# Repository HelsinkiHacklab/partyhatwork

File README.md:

partyhatwork
============

Mesh network of [party][party1]-[hats][hat1], see http://kirjoitusalusta.fi/hacklab-partyhatwork

[party1]: http://www.youtube.com/watch?v=EIru0xmfsWs
[hat1]: http://www.flickr.com/photos/netlcom/7639700776/in/pool-hlt

## Hardware

  * [rev1](./hardware/board_rev1/)

## Software

  * Reference XMegaduino [sketch](./software/arduino/partyhatwork/)
  * [Instructions](https://github.com/HelsinkiHacklab/XMega-boards/tree/master/software/arduino-xmega) for patching XMegaduino to support our board variant
  * [XBee API wrapper](./software/pc/beehive)
  * [Animation builder](http://helsinkihacklab.github.io/partyhatwork/software/pc/animationbuilder/animationbuilder.html)

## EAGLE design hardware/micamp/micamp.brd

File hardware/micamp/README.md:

# Microphone board

Basically this [sparkfun board][sparkmic] but with better mic and suitably adjusted filter values.

[sparkmic]: https://www.sparkfun.com/products/9964

## BOM

  - http://www.digikey.fi/product-detail/en/CMA-4544PF-W/102-1721-ND/1869981
  - http://www.digikey.fi/product-detail/en/OPA344NA%2F250/OPA344NACT-ND/362263
  - Some standard 0603 size caps & resistors which I will enumerate later

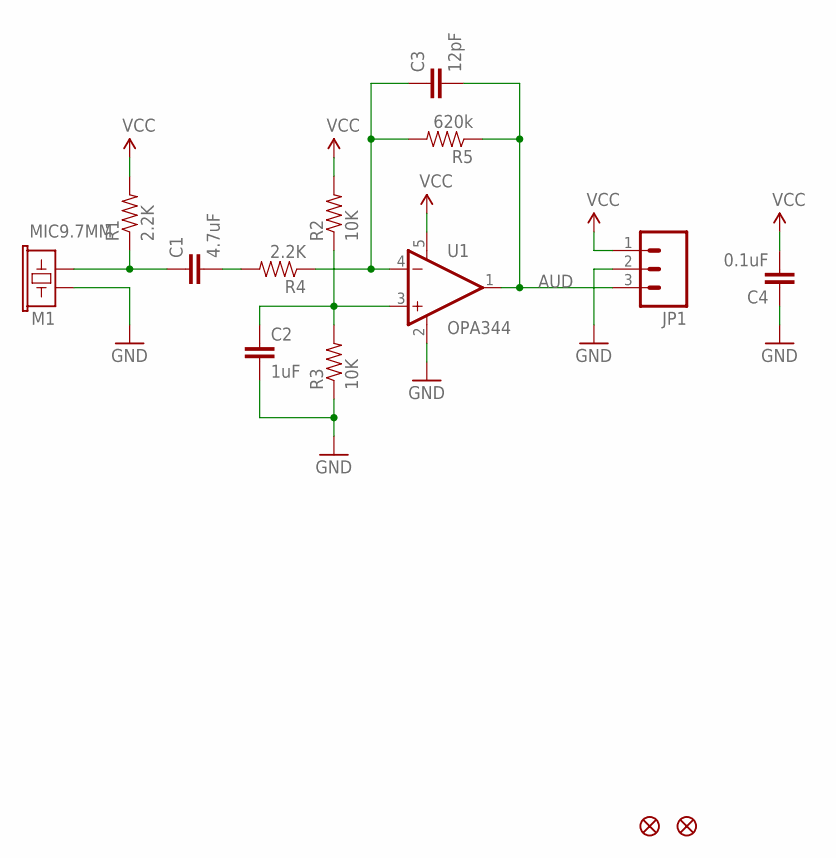
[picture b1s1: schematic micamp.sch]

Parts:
C1: 4.7uF; 0603-CAP
C2: 1uF; 0603-CAP
C3: 12pF; 0603-CAP
C4: 0.1uF; 0603-CAP
JP1: M03PTH; 1X03
JP2, JP3: FIDUCIAL1X2; FIDUCIAL-1X2
M1: MIC9.7MM; MIC-9.7MM
R1, R4: 2.2K; 0603-RES
R2, R3: 10K; 0603-RES
R5: 620k; 0603-RES
U1: OPA344; SOT23-5

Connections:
AUD: C3.2, JP1.3, R5.1, U1.1 (OUT)
GND: C2.2, C4.1, JP1.2, M1.2, R3.1, U1.2 (V-)
unnamed: C1.1, M1.1, R1.1
unnamed: C3.1, R4.1, R5.2, U1.4 (-IN)
unnamed: C1.2, R4.2
unnamed: C2.1, R2.1, R3.2, U1.3 (+IN)
VCC: C4.2, JP1.1, R1.2, R2.2, U1.5 (V+)

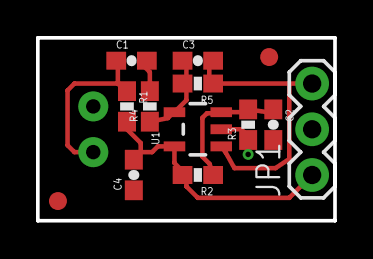
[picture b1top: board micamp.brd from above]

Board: 2 copper layers, 16.5 x 10.2 mm, 14 parts (1 on the bottom side), 7 nets.

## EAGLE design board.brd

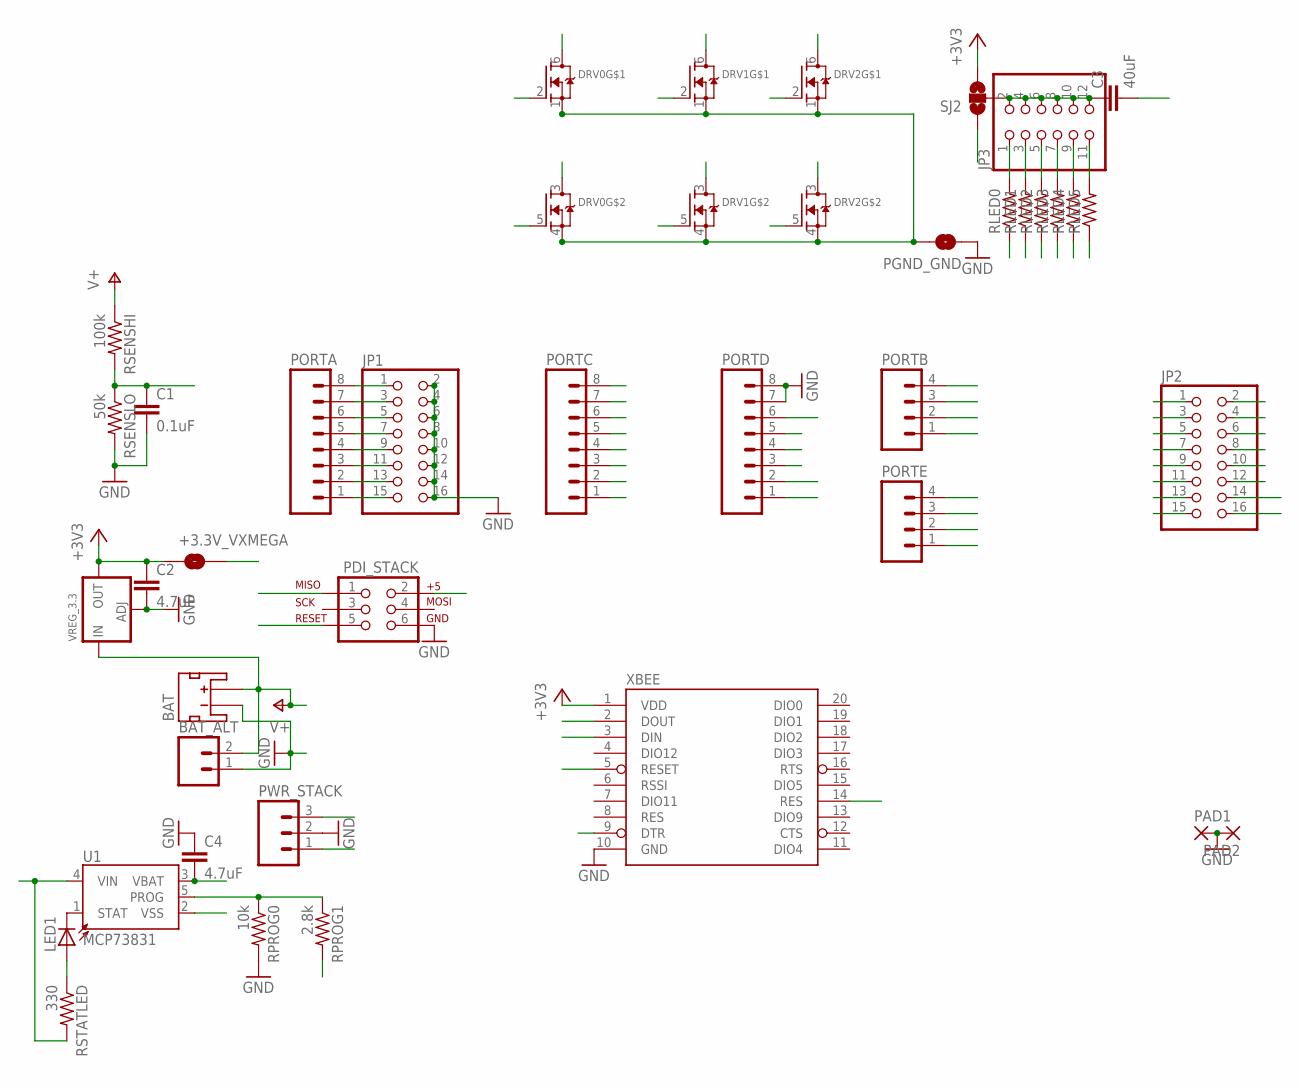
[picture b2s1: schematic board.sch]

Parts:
+3.3V_VXMEGA: SOLDERJUMPERTRACE; SJ_2S-TRACE
BAT: JST_2MM_MALE; JST-2-SMD
BAT_ALT: M02PTH; 1X02
C1: 0.1uF; C0603K
C2: 4.7uF; C0805K
C3: 40uF; C1210
C4: 4.7uF; C0805
DRV0, DRV1, DRV2: MOSFET-N_DUAL; SOT363
JP1: PINHD-2X8; 2X08
JP2: PINHD-2X8/90; 2X08/90
JP3: PINHD-2X6/90; 2X06/90
LED1: LEDCHIP-LED0603; CHIP-LED0603
PAD1, PAD2: 3,81/1,4
PDI_STACK: AVR_SPI_PRG_6NS; 2X3-NS
PGND_GND: SOLDERJUMPERTRACE; SJ_2S-TRACE
PORTA: M081X08; 1X08
PORTB: M04PTH; 1X04
PORTC: M081X08; 1X08
PORTD: M081X08; 1X08
PORTE: M04PTH; 1X04
PWR_STACK: M03PTH; 1X03
RLED0, RLED1, RLED2, RLED3, RLED4, RLED5: R-US_R0805; R0805
RPROG0: 10k; R0603
RPROG1: 2.8k; R0603
RSENSHI: 100k; R0603
RSENSLO: 50k; R0603
RSTATLED: 330; R0603
SJ2: SOLDERJUMPER_2WAY-OLDT; SJ_2
U1: MCP73831; SOT23-5
VREG_3.3: LM1117SOT223-WAVE; SOT223-W
XBEE: XBEE-1B2; XBEE-SILK

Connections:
+3V3: +3.3V_VXMEGA.1, C2.1, JP2.2, SJ2.3, VREG_3.3.2 (OUT), XBEE.1 (VDD)
GND: BAT.1 (-), BAT_ALT.1, C1.2, C2.2, C4.1, JP1.2, JP1.4, JP1.6, JP1.8, JP1.10, JP1.12, JP1.14, JP1.16, JP2.4, JP2.13, PAD1.1, PAD2.1, PDI_STACK.6, PGND_GND.1, PORTD.7, PORTD.8, PWR_STACK.2, RPROG0.2, RSENSLO.2, U1.2 (VSS), VREG_3.3.1 (ADJ), XBEE.10 (GND), XBEE.14 (RES)
LED0: DRV0.6 (D), RLED0.1
LED0R: JP3.1, RLED0.2
LED1: DRV0.3 (D), RLED1.1
LED1R: JP3.3, RLED1.2
LED2: DRV1.6 (D), RLED2.1
LED2R: JP3.5, RLED2.2
LED3: DRV1.3 (D), RLED3.1
LED3R: JP3.7, RLED3.2
LED4: DRV2.6 (D), RLED4.1
LED4R: JP3.9, RLED4.2
LED5: DRV2.3 (D), RLED5.1
LED5R: JP3.11, RLED5.2
unnamed: LED1.C, U1.1 (STAT)
unnamed: LED1.A, RSTATLED.1
PA0: JP1.15, PORTA.1
PA1: JP1.13, PORTA.2
PA2: JP1.11, PORTA.3
PA3: JP1.9, PORTA.4
PA4: JP1.7, PORTA.5
PA5: JP1.5, PORTA.6
PA6: JP1.3, PORTA.7
PA7: JP1.1, PORTA.8
PB0/XMEGA_AREF: JP2.1, PORTB.1, RPROG1.2
PB1/VBAT_SENSE: C1.1, JP2.3, PORTB.2, RSENSHI.2, RSENSLO.1
PB2: JP2.5, PORTB.3
PB3: JP2.7, PORTB.4
PD0: JP2.9, PORTD.1
PD1: JP2.11, PORTD.2
PD5: JP2.15, PORTD.6
PDI_DATA: PDI_STACK.1
PDI_RESET/CLK: PDI_STACK.5, XBEE.9 (DTR)
PE0/SDA: JP2.6, PORTE.1
PE1/SCL: JP2.8, PORTE.2
PE2: JP2.10, PORTE.3
PE3: JP2.12, PORTE.4
PGND: C3.2, DRV0.1 (S), DRV0.4 (S), DRV1.1 (S), DRV1.4 (S), DRV2.1 (S), DRV2.4 (S), PGND_GND.2
PWM0: DRV0.2 (G), PORTC.1
PWM1: DRV0.5 (G), PORTC.2
PWM2: DRV1.2 (G), PORTC.3
PWM3: DRV1.5 (G), PORTC.4
PWM4: DRV2.2 (G), PORTC.5
PWM5: DRV2.5 (G), PORTC.6
RPROG: RPROG0.1, RPROG1.1, U1.5 (PROG)
VBAT: BAT.2 (+), BAT_ALT.2, C4.2, RSENSHI.1, SJ2.1, U1.3 (VBAT), VREG_3.3.3 (IN)
VLED: C3.1, JP3.2, JP3.4, JP3.6, JP3.8, JP3.10, JP3.12, SJ2.2
VXMEGA: +3.3V_VXMEGA.2, PDI_STACK.2, PWR_STACK.3
VXMEGA_USB: PWR_STACK.1, RSTATLED.2, U1.4 (VIN)
XBEE_RESET: PORTD.5, XBEE.5 (RESET)
XMEGA_RX0: PORTD.3, XBEE.2 (DOUT)
XMEGA_RX1: JP2.14, PORTC.7
XMEGA_TX0: PORTD.4, XBEE.3 (DIN)
XMEGA_TX1: JP2.16, PORTC.8

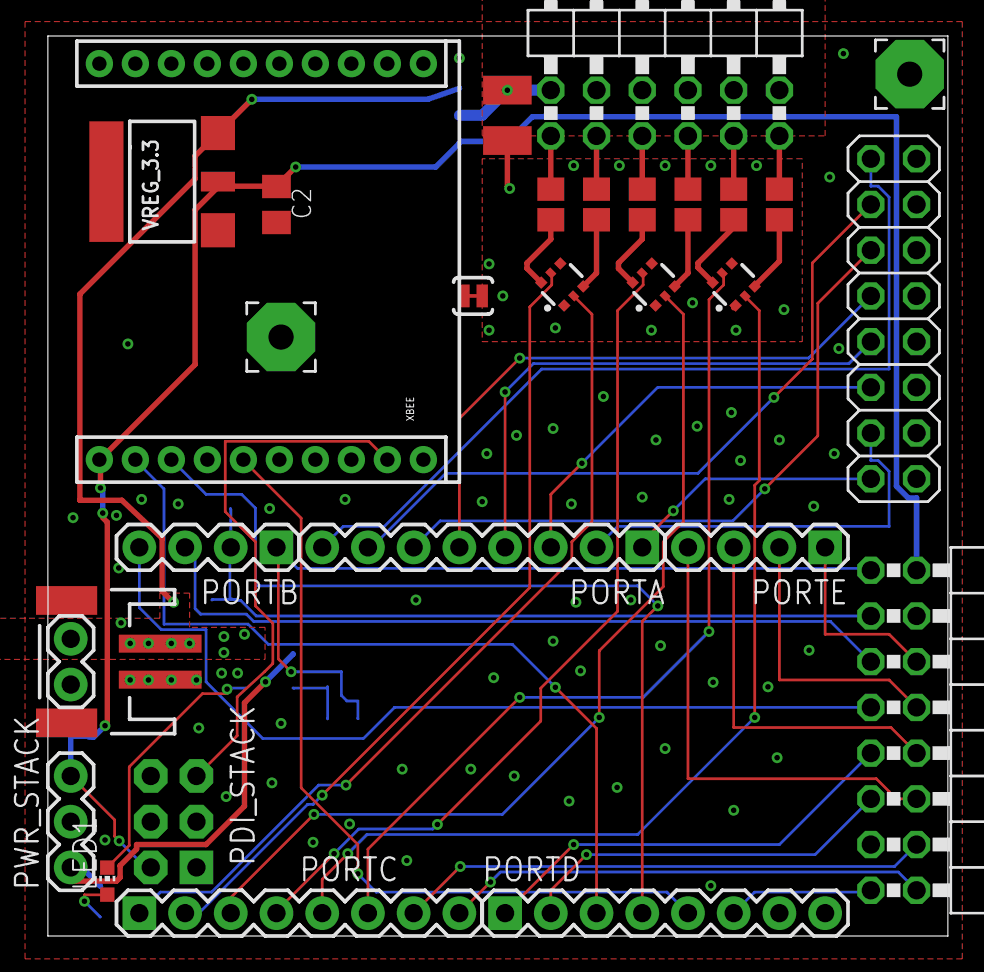
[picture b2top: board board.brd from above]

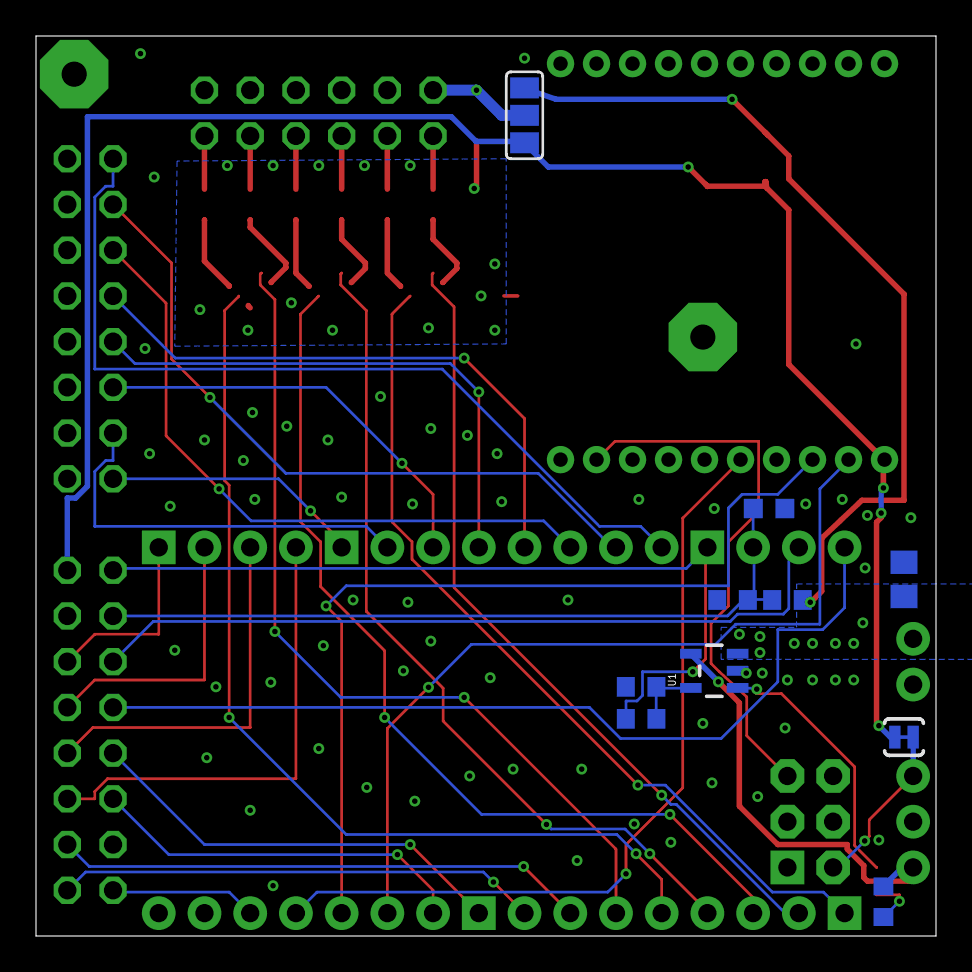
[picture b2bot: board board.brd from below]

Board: 2 copper layers, 50.0 x 50.0 mm, 39 parts (10 on the bottom side), 53 nets.

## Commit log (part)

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2012-11-21 started working on the xbee+darlington "shield" for https://raw.github.com/HelsinkiHacklab/XMega-boards/master/Xmega32A4U.jpg
2012-11-21 minor updates
2012-11-21 placing a stacking header so we can get reset and 3.3v from the xmega board
2012-11-21 stack the power connector too and mark out the 50x50mm board area for cheapest chinese boards
2012-11-21 use the stub portd for rx/tx in case someone is using the rtc xtal on porte
2012-11-21 reposition the xmega stacking headers, move the xbee breakout to top-left corner
2012-11-21 some notes
2012-11-21 noted the second UART
2012-11-21 we have 6 HW pwm-channels, so add that many dual-mosfets
2012-11-21 add general ground pours
2012-11-21 added JST battery connector, alternatively 2.54mm pin header can be used
2012-11-22 this header must be 90deg one, otherwise it will not fit under the xbee
2012-11-22 bigger cap for the leds
2012-11-22 xbee and xmega share aref
2012-11-22 connecting rest of the ports
2012-11-22 adjust the AGND polygon
2012-11-22 routed the analog signals manualle
2012-11-22 smaller agnd polygon
2012-11-22 Seeed DRU
2012-11-22 autorouter setup
2012-11-22 wrong class (and moved the xbee a bit
2012-11-22 on a second thought, do not put that power pin in the middle of the connector...
2012-11-22 smaller isolations
2012-11-22 put the agnd polygon on top layer too
2012-11-22 angle the mosfets in hopes of getting the power signals router better
2012-11-22 12mils will have to be enough
2012-11-22 routed, not very nice or optimal I guess, but it should work
2012-11-22 mark the jumper resistor values
2012-11-22 freeroute.net base routing and adjustments + gnd vias on top
2012-11-23 get rid of agnd
2012-11-23 the xbee aref is not used on series2 anyway
2012-11-23 adjust some vias
2012-11-23 version without agnd (but needs no jumper-resistors), the lipo-charger is still missing
2012-11-23 placed lipo-charger second R that could be used to enable higher chg current via the UC
2012-11-23 in wonder what I did there
2012-11-23 100mA charge current normally, sink PD5 to GND to make it 500mA
2012-11-23 lipo-chg in place (I hope)
2012-11-23 connecting planes
2012-11-23 now I need to route that on 3.3v
2012-11-23 handle ERC
2012-11-23 handle DRC
2012-11-23 updated readme, added some extra vias to pgnd
2012-11-23 remove thermals from PGND
2012-11-23 hide the airwire, it is connected on the xmega board
2012-11-23 forgot to re-route after fixing a signal name
2012-11-23 add two large pads that hopefully help with mounting
2012-11-23 link to correct charge chip
2012-11-23 updated BOM
2012-11-23 link to xbee header source
2012-12-10 sourcing information
2012-12-16 invoked labels
2012-12-16 hanled some DRCs
2012-12-16 reorganizing
2012-12-21 Binary patched DFU-bootloaders with different sense pins
2012-12-22 formatting fixes
2013-02-02 the xmega repo is slitghly reorganized
2013-02-02 patching xmegaduino
2013-02-02 started writing pin mappings
2013-02-02 todos
2013-02-02 pin mappings
2013-02-02 typo fix, moar mappings
2013-02-02 mappings
2013-02-02 typo fixes in mappings
2013-02-02 this probably is the correct way to map channel with the value returned from digital_pin_to_timer_PGM
2013-02-02 the old mappings should not have been touched
2013-02-02 see previous
2013-02-02 instructions
2013-02-03 stub sketchä
2013-02-03 pin numbers start from 0
2013-02-03 init xbee wrapper
2013-02-03 trivial pwm value setting over xbee
2013-02-03 fix off-by-one error
2013-02-03 the scaling fails
2013-02-03 moved the Arduino patches to the repo housing the xmega board designs
2013-02-04 UNTESTED: refactor to task/event based approach
2013-02-04 remind about that bug
2013-02-04 the xbee callback setting via constructor did work earlier
2013-02-04 wtf I did go back to the old way...
2013-02-04 the compile-error is apparently related to the auto-prototyper, see http://code.google.com/p/arduino/issues/detail?id=188
2013-02-04 and this now compiles, wtf ?
2013-02-10 run the given RGB values through gamma-correction to get the PWM-value (which is then adjusted based on battery voltage)
2013-02-10 reorg
2013-02-10 safeties
2013-02-10 added README
2013-02-10 minor update
2013-02-10 this way the batterymonitor at least compiles
2013-02-10 the official xbee module is b0rked, use a fork
2013-02-10 bootloaders are software
2013-02-10 a sleep task, not really tested yet
2013-02-10 clarify comments
2013-02-10 pulse a pin when not sleeping
2013-02-10 blink a led every 1s
2013-02-10 sanity check
2013-02-10 Added xbee_test.py to send some test data to the hats.
2013-02-10 move to separate dir and keep the modem port in inifile
2013-02-10 dumps serial port output
2013-02-10 normalize whitespace
2013-02-12 gah, start() is needed
2013-02-12 parse addressed from inifile
2013-02-12 script for testing config parsing
2013-02-12 sane default for as example, helper and documentation
2013-02-12 very simple launcher and node wrapper
2013-02-12 separete the handler to different module while it is simple
2013-02-12 do not track the inifile
2013-02-12 make an importable module
2013-02-12 automagical packing
2013-02-13 painfull lessons
2013-02-13 stub
2013-02-13 stub stock arduino sketch to test just the animations (and idle sleep since that might affect them)
2013-02-13 make this first work on SRAM, worry about PROGMEM and EEPROM later
2013-02-13 testing struct passing
2013-02-13 calculate frame size based on led count
2013-02-13 the frame pointer passing is somehow borked now, will think about it later
2013-02-13 it almost works, there is probably an off-by-one error somewhere
2013-02-13 should not have overloaded that method
2013-02-13 it works better now but the wait_ms is still wrong
2013-02-14 noted the regulator pinout as a bug
2013-02-14 oops...
2013-02-14 the linked-list solution to loading the desired animation works too
2013-02-20 fixed image url
2013-03-08 move the frame data to PROGMEM
2013-03-08 hunting for errors in the wrong places...
2013-03-08 it works now for loading from progmem
2013-03-09 ok this works now
2013-03-09 move the animations to separate header
2013-03-09 remove the SRAM frame unpacker, it is not going to be used anymore
2013-03-09 started writing the state machine required for fading
2013-03-09 well that was dumb...
2013-03-09 be able to unpack multiple frames
2013-03-09 more untested but compiling stuff
2013-03-09 there is still some issu in handling full step transitions but the fade interpolations seems to work
2013-03-09 minor refactoring for more readable code
2013-03-09 this actually should not work almost correctly
2013-03-09 comment out the fade interpolation debug, we see it moment later in the leds set method anyway
2013-03-09 this was the wrong way around
2013-03-09 ok, now this is looking good
2013-03-09 copied the animation code from animationtests
2013-03-09 fix references
2013-03-09 forgot to add this file
2013-03-09 XBee.h must be included early it seems
2013-03-09 fix missing breaks
2013-03-09 testing the xbee protocol
2013-03-09 do not try to reset the animation state
2013-03-09 Better sRGB gamma table for LEDs
2013-03-09 the correct declaration for PROGMEM data is const type
2013-03-15 started work on diffusor reflector plans so did a bit of reorg
2013-03-16 plot the measured points
2013-03-16 copy the bezier code from the example
2013-03-16 heh close on the second questimate
2013-03-16 even closer
2013-03-16 will be using openscad to model the reflector even if it will be in 2D (maybe I will adjust the bezier lib to skip those linear_extruders soon, or maybe I will just project the "3D" model back to 2D)
2013-03-16 very close
2013-03-16 looking very good
2013-03-16 should have used 110 as the mug lenght on these, the control points look good enough still
2013-03-16 use the inner measures and add some comments
2013-03-16 comments
2013-03-16 add reflector bottom
2013-03-16 add nothes to the bend-line
2013-03-16 almost ok, but maybe I will try fitting a bezier to this too
2013-03-16 made the mug bottom
2013-03-16 added some render-calls
2013-03-16 the paper model was too tight, adjusted points and refit the curve
2013-03-16 adjusted the dimensions, paper-model testing showed it was a bit too tight previously
2013-03-16 template for manual cutting
2013-03-16 updated with instructions
2013-03-16 more space for cutting (I had to use a guillotine to manage separate the two pieces before using tin-snips to shape them)
2013-03-16 px vs mm and noted tha new spacing
2013-03-17 added assembly photos
2013-03-17 notes on regulators
2013-03-20 alternative charge chip
2013-03-20 started a stub QML GUI for defining animations
2013-03-20 bah it seems making this in pure QML is going to be complex (lack of widgets...)
2013-03-22 I guess HTML is the quickest cross-platform way
2013-03-22 names to ids, no need for names here
2013-03-22 frame inputs creation
2013-03-22 input the RGB via a color picker to single input field
2013-03-22 more form management
2013-03-22 started working on the animation handler class
2013-03-23 fleshing out...
2013-03-23 just stick with reload
2013-03-23 sanity checks etc
2013-03-23 hard transitions work
2013-03-23 animation code generation, part 1
2013-03-23 clear generated code whenever assumptions about it change
2013-03-23 some clarifications
2013-03-23 fade code, has still some weird bug...
2013-03-23 what gives here ?
2013-03-23 oops, the hex code widths, but there is a real bug too, it will need to be hunted down when more awake
2013-03-23 found the bug in this fade code
2013-03-23 less noise to console
2013-03-23 stop animation when generating code
2013-03-24 add a mic, maybe
2013-03-24 link to the opamp sparkfun uses
2013-04-04 links to video & photo
2013-04-08 typo fix
2013-05-14 Basic standalone demos for xmega development
2013-05-14 Moved to HelsinkiHacklab / XMega-boards
2013-05-18 naming conventions
2013-05-18 better demo mode, cycle through the animations we have defined in animations.h
2013-05-18 clarifying program logic
2013-05-29 adjusted schema
2013-05-29 list parts
2013-05-29 switch to 0603 package which is still hand-solderable
2013-05-29 link to the just made mic board
2013-06-25 working on the eeg stuff, and make those private properties protected so I can access them in the subclass
2013-06-25 override the unpack_frame
2013-06-25 work-in-progress
2013-06-28 doing a bit of reorganizing
2013-06-28 clarified comments
2013-06-28 one more xbee serial port reference
2013-06-28 send TGAM data to coordinator (if defined)
2013-06-28 the brain stuff does not seem to work...
2013-06-28 apparently the serial.begin cannot be called in the consctructor
2013-06-28 fix indent
2013-06-28 once I fugure which colors to use (and get actually usable signal quality..) this *should* fade between colors according to strongest band of brainwaves
2013-06-29 the HSV space EEG color choosing logic
2013-06-29 forgot the mode flags from the animation, this now sorta works with the mindband (still getting poor signal from my homemade TGAM breakout and electrodes)
2013-06-29 add a bit more variation to the S and V parts of the color
2013-06-29 report the packets bitfield over xbee, and check that (at least in theory) we have attention and meditation values before trying to use them
2013-06-29 more variance by averaging the hue of the two strongest bands
2013-07-07 remove the trobe from animation list for now, it causes headache, reorder tasks for smoother animation
2013-07-07 add enable/disable command for the EEG, it causes huge interrupt pressure due to the 52700 serial port speed and 200Hz data rate
2013-08-02 xbee profile files for hat and coordinator
2013-08-02 disable EEG, enable strobe animation
2013-08-02 pages test
2013-08-02 lets see if this works
2013-08-03 it seems newer versio of this library autostarts the thread
2013-08-03 update links
2013-08-03 memoes
2013-09-03 helper for sending (ascii) strings

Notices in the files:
parts and their libraries:
SparkFun-RF: Licensing: CC v3.0 Share-Alike You are welcome to use this library for commercial purposes.
microbuilder: This work is placed in the public domain, and may be freely used for commercial and non-commercial work with the following conditions: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
